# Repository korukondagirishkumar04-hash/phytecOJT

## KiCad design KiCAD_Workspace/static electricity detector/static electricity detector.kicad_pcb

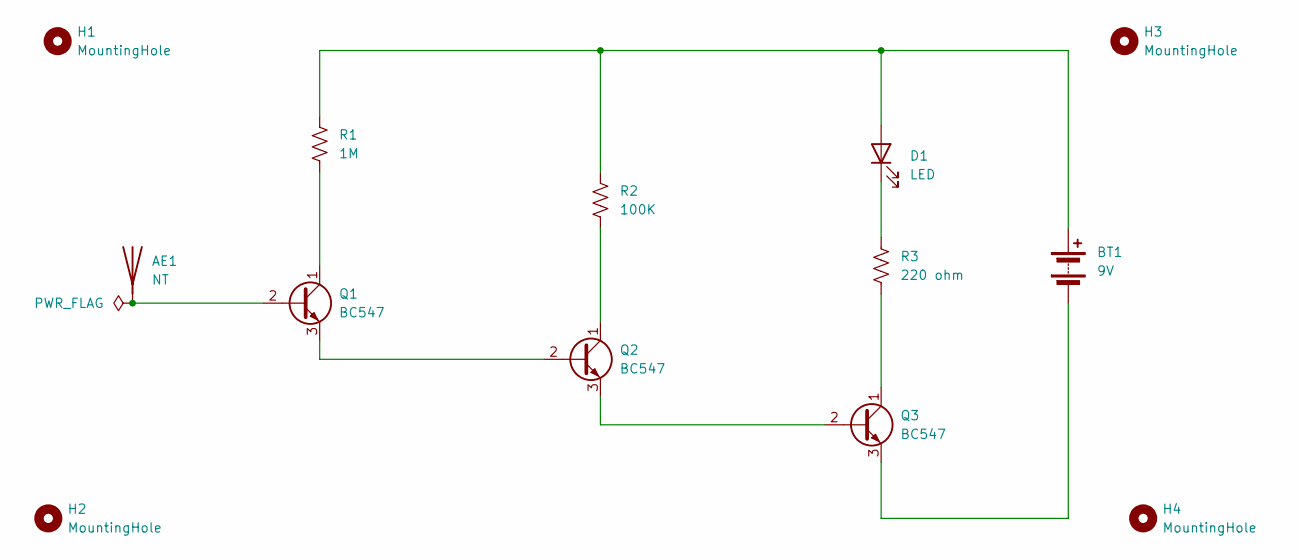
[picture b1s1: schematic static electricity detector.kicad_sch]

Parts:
AE1: NT; PinHeader_1x01_P2.54mm_Vertical
BT1: 9V; BatteryHolder_Keystone_3000_1x12mm
D1: LED; LED_D5.0mm
H1, H2, H3, H4: MountingHole; MountingHole_3.2mm_M3_Pad
Q1, Q2, Q3: BC547; TO-92_Inline
R1: 1M; R_Axial_DIN0207_L6.3mm_D2.5mm_P7.62mm_Horizontal
R2: 100K; R_Axial_DIN0207_L6.3mm_D2.5mm_P7.62mm_Horizontal
R3: 220 ohm; R_Axial_DIN0207_L6.3mm_D2.5mm_P7.62mm_Horizontal

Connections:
unnamed: AE1.1 (A_1), Q1.2 (B)
unnamed: BT1.1 (+), D1.2 (A), R1.1, R2.1
unnamed: BT1.2 (-), Q3.3 (E)
unnamed: D1.1 (K), R3.1
unnamed: Q1.1 (C), R1.2
unnamed: Q1.3 (E), Q2.2 (B)
unnamed: Q2.1 (C), R2.2
unnamed: Q2.3 (E), Q3.2 (B)
unnamed: Q3.1 (C), R3.2

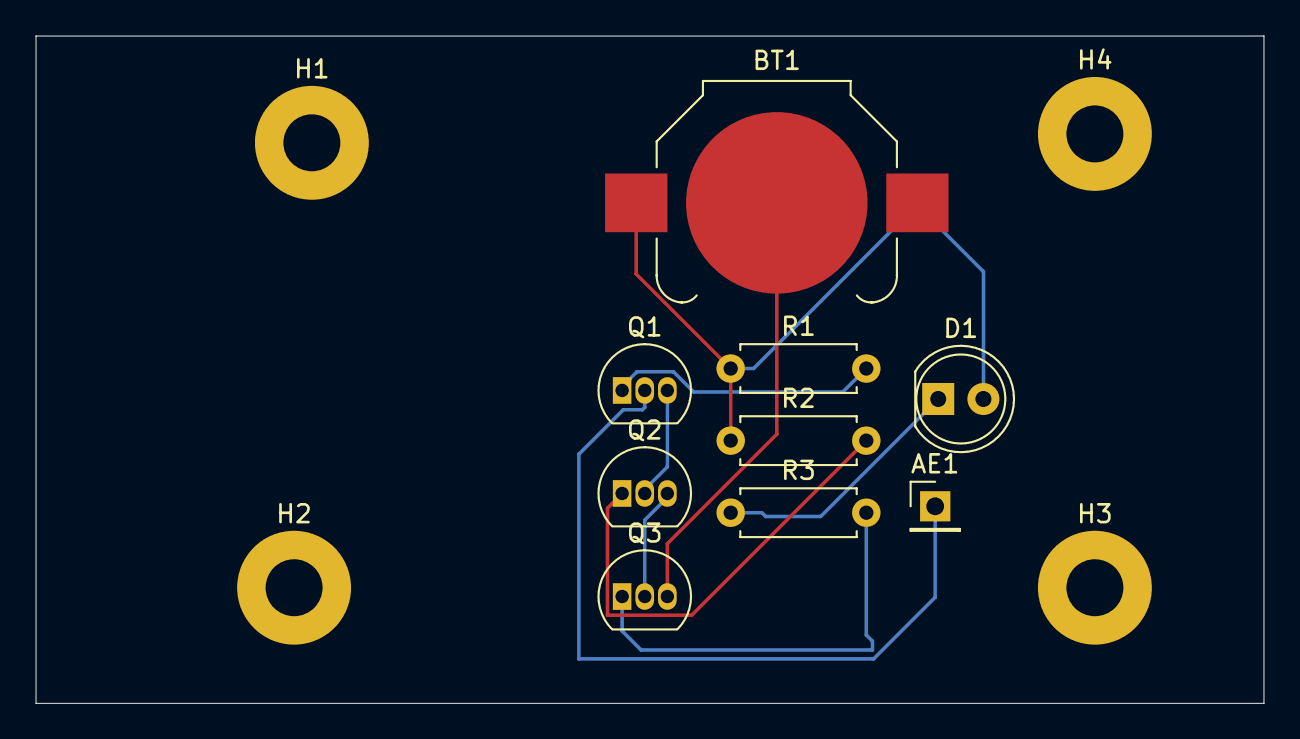
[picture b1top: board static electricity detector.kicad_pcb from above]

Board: 2 copper layers, 69.0 x 37.5 mm, 13 parts (0 on the bottom side), 9 nets.

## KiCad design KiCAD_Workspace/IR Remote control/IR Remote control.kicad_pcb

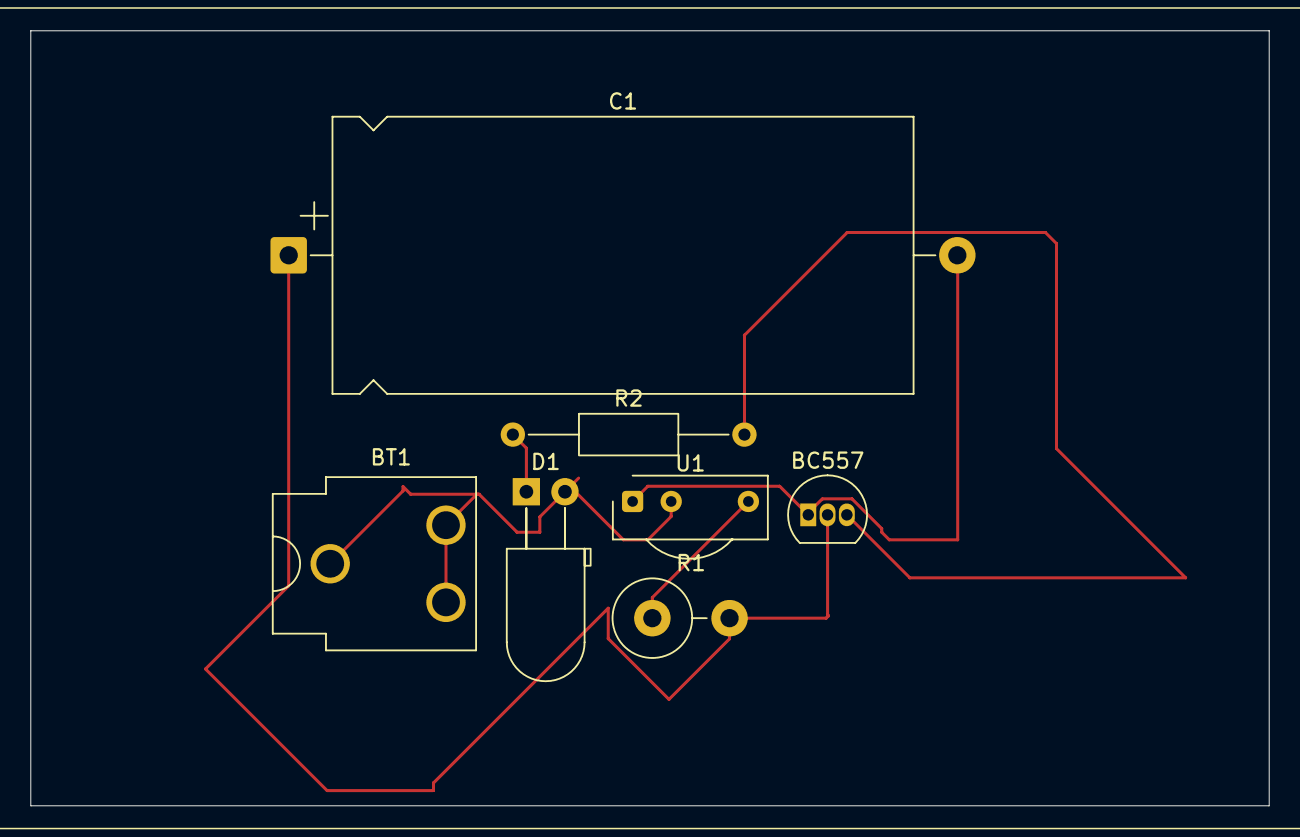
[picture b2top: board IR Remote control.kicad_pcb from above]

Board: 2 copper layers, 81.5 x 51.0 mm, 7 parts (0 on the bottom side), 6 nets.

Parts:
BC557: TO-92_Inline
BT1: 9V; BatteryClip_Keystone_54_D16-19mm
C1: C_US; CP_Axial_L38.0mm_D18.0mm_P44.00mm_Horizontal
D1: LED; LED_D5.0mm_Horizontal_O3.81mm_Z15.0mm
R1: 1K; R_Axial_DIN0516_L15.5mm_D5.0mm_P5.08mm_Vertical
R2: 220; R_Axial_DIN0207_L6.3mm_D2.5mm_P15.24mm_Horizontal
U1: TSOP17xx; Vishay_CAST-3Pin

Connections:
unnamed: BC557.2 (B), C1.1, R1.2
unnamed: BC557.1 (C), C1.2, U1.1 (GND)
unnamed: BC557.3 (E), R2.2
unnamed: BT1.1 (+_1), D1.2 (A), U1.2 (Vs)
unnamed: D1.1 (K), R2.1
unnamed: R1.1, U1.3 (OUT)

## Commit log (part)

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2026-02-24 day1
2026-02-27 day2
2026-02-28 day3
2026-03-05 day4
2026-03-07 day5
2026-03-07 deleted unused files
2026-03-07 restore files
2026-03-07 restore
2026-05-19 Workspace
2026-05-19 IR Remote control
2026-05-20 c_workspace
